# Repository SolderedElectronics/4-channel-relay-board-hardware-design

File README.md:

# 4-channel relay board  Hardware Design

## About the Product

|  |
| :----------------------------------------------------------: |
| [Buy 4-channel relay board ](https://www.solde.red/333022) |

Did you ever want to turn on and off a device that needs large current or voltage? Whether operating on DC or AC, a relay is what you need. A relay is actually an electronic switch that is activated by a signal we send from a Dasduino or Arduino. This module further simplifies the whole process because it contains everything you need for the relay to work, and you just have to connect it to the microcontroller and power supply. You don’t have to think about voltages and currents, insulation between high and low voltage or grounding, everything is already taken care of on the board. This product has 4 relays.

---

## Repository Contents

This repository contains all design files for 4-channel relay board , organized as follows:

- **`CAD` folder**: Contains KiCAD design files, including:
  - Schematics
  - PCB layout
  - Panel PCB layout
  - Source 3D files in Fusion360, if any
  - All files are sorted by version with a detailed change log.
- **`OUTPUTS` folder**: Includes all production-ready files, such as:
  - Bill of Materials (BOM) and interactive BOM (iBOM)
  - PDF versions of schematics
  - 3D `.step` file of the board
  - 3D-printable models
  - Gerber files for PCB manufacturing
  - Image of the pinout of the board
  - Product image
  - Compliance, legal and generic sales documents

Refer to the `Change Log` in the CAD folder for details about updates between versions.

---

## Learn More About the Product

Beyond the repository, explore the following resources:

### Soldered Verify

The **Soldered Verify** system ensures every board you purchase from Soldered is fully functional. It also provides access to exclusive test data for your product. To get started, find the unique Soldered Verify ID on your product's packaging and enter the ID on the [Soldered Verify page](https://soldered.com/verify/) to access test results and additional product details.

### Soldered Community

Soldered Community is your go-to place for technical support. Our engineers track and answer all questions posted there, and it’s a great space for the maker community. Get answers to your questions and solutions for your challenges at [Soldered Community](https://soldered.com/community).

### solde.red

solde.red is an ultimate URL shortener and information hub. Access it by typing solde.red/ followed by your product SKU, e.g., [solde.red/333000](https://solde.red/333000), to find getting-started guides, datasheets, open-source hardware and software files, certifications, images, pinouts, and more. Read more about the shortener [here](https://solde.red/info/).

---

## Contributing

Contributions are welcome! Here’s how you can get involved:

- Submit pull requests to enhance the design or fix issues.
- Report bugs or problems by opening an issue.

We encourage community collaboration to make this product even better.

---

## About Soldered

[Soldered for Makers](https://soldered.com) specializes in designing and manufacturing electronic products tailored for enthusiasts, ranging from hobbyists to professionals. Our portfolio includes electronic boards, sensors, and actuators that are widely utilized in fields such as microelectronics, mechatronics, robotics, programming, and IoT. Every product we offer is designed in-house and built upon open-source hardware and software platforms. Proudly certified and manufactured within the European Union, our catalog likely includes the product you need for your project.

We complement these products with comprehensive tutorials and manuals, product descriptions, schematics, programming codes, and project examples. Our round-the-clock [customer and technical support](https://soldered.com/community) is available for all our products, irrespective of the sales channel. Soldered’s success and services reflect our maker community’s unwavering [trust](https://www.trustpilot.com/review/soldered.com), for which we are deeply grateful. Join our community and create using Soldered products.

---

## License

All Soldered open-source hardware (OSH) is under The TAPR Open Hardware License. Read more in the LICENSE file located in this repository.

**Disclaimer:**

No warranty - all designs in this repository are distributed in the hope that they will be useful, but without any warranty. They are provided "AS IS", therefore without warranty of any kind, either expressed or implied. The entire quality and performance of what you do with the contents of this repository are your responsibility. In no event Soldered Electronics will be liable for your damages, or losses, including any general, special, incidental, or consequential damage arising out of the use or inability to use the contents of this repository. 

---

## Have fun!

Thank you for your support from your fellow makers at Soldered Electronics.

Happy Making!

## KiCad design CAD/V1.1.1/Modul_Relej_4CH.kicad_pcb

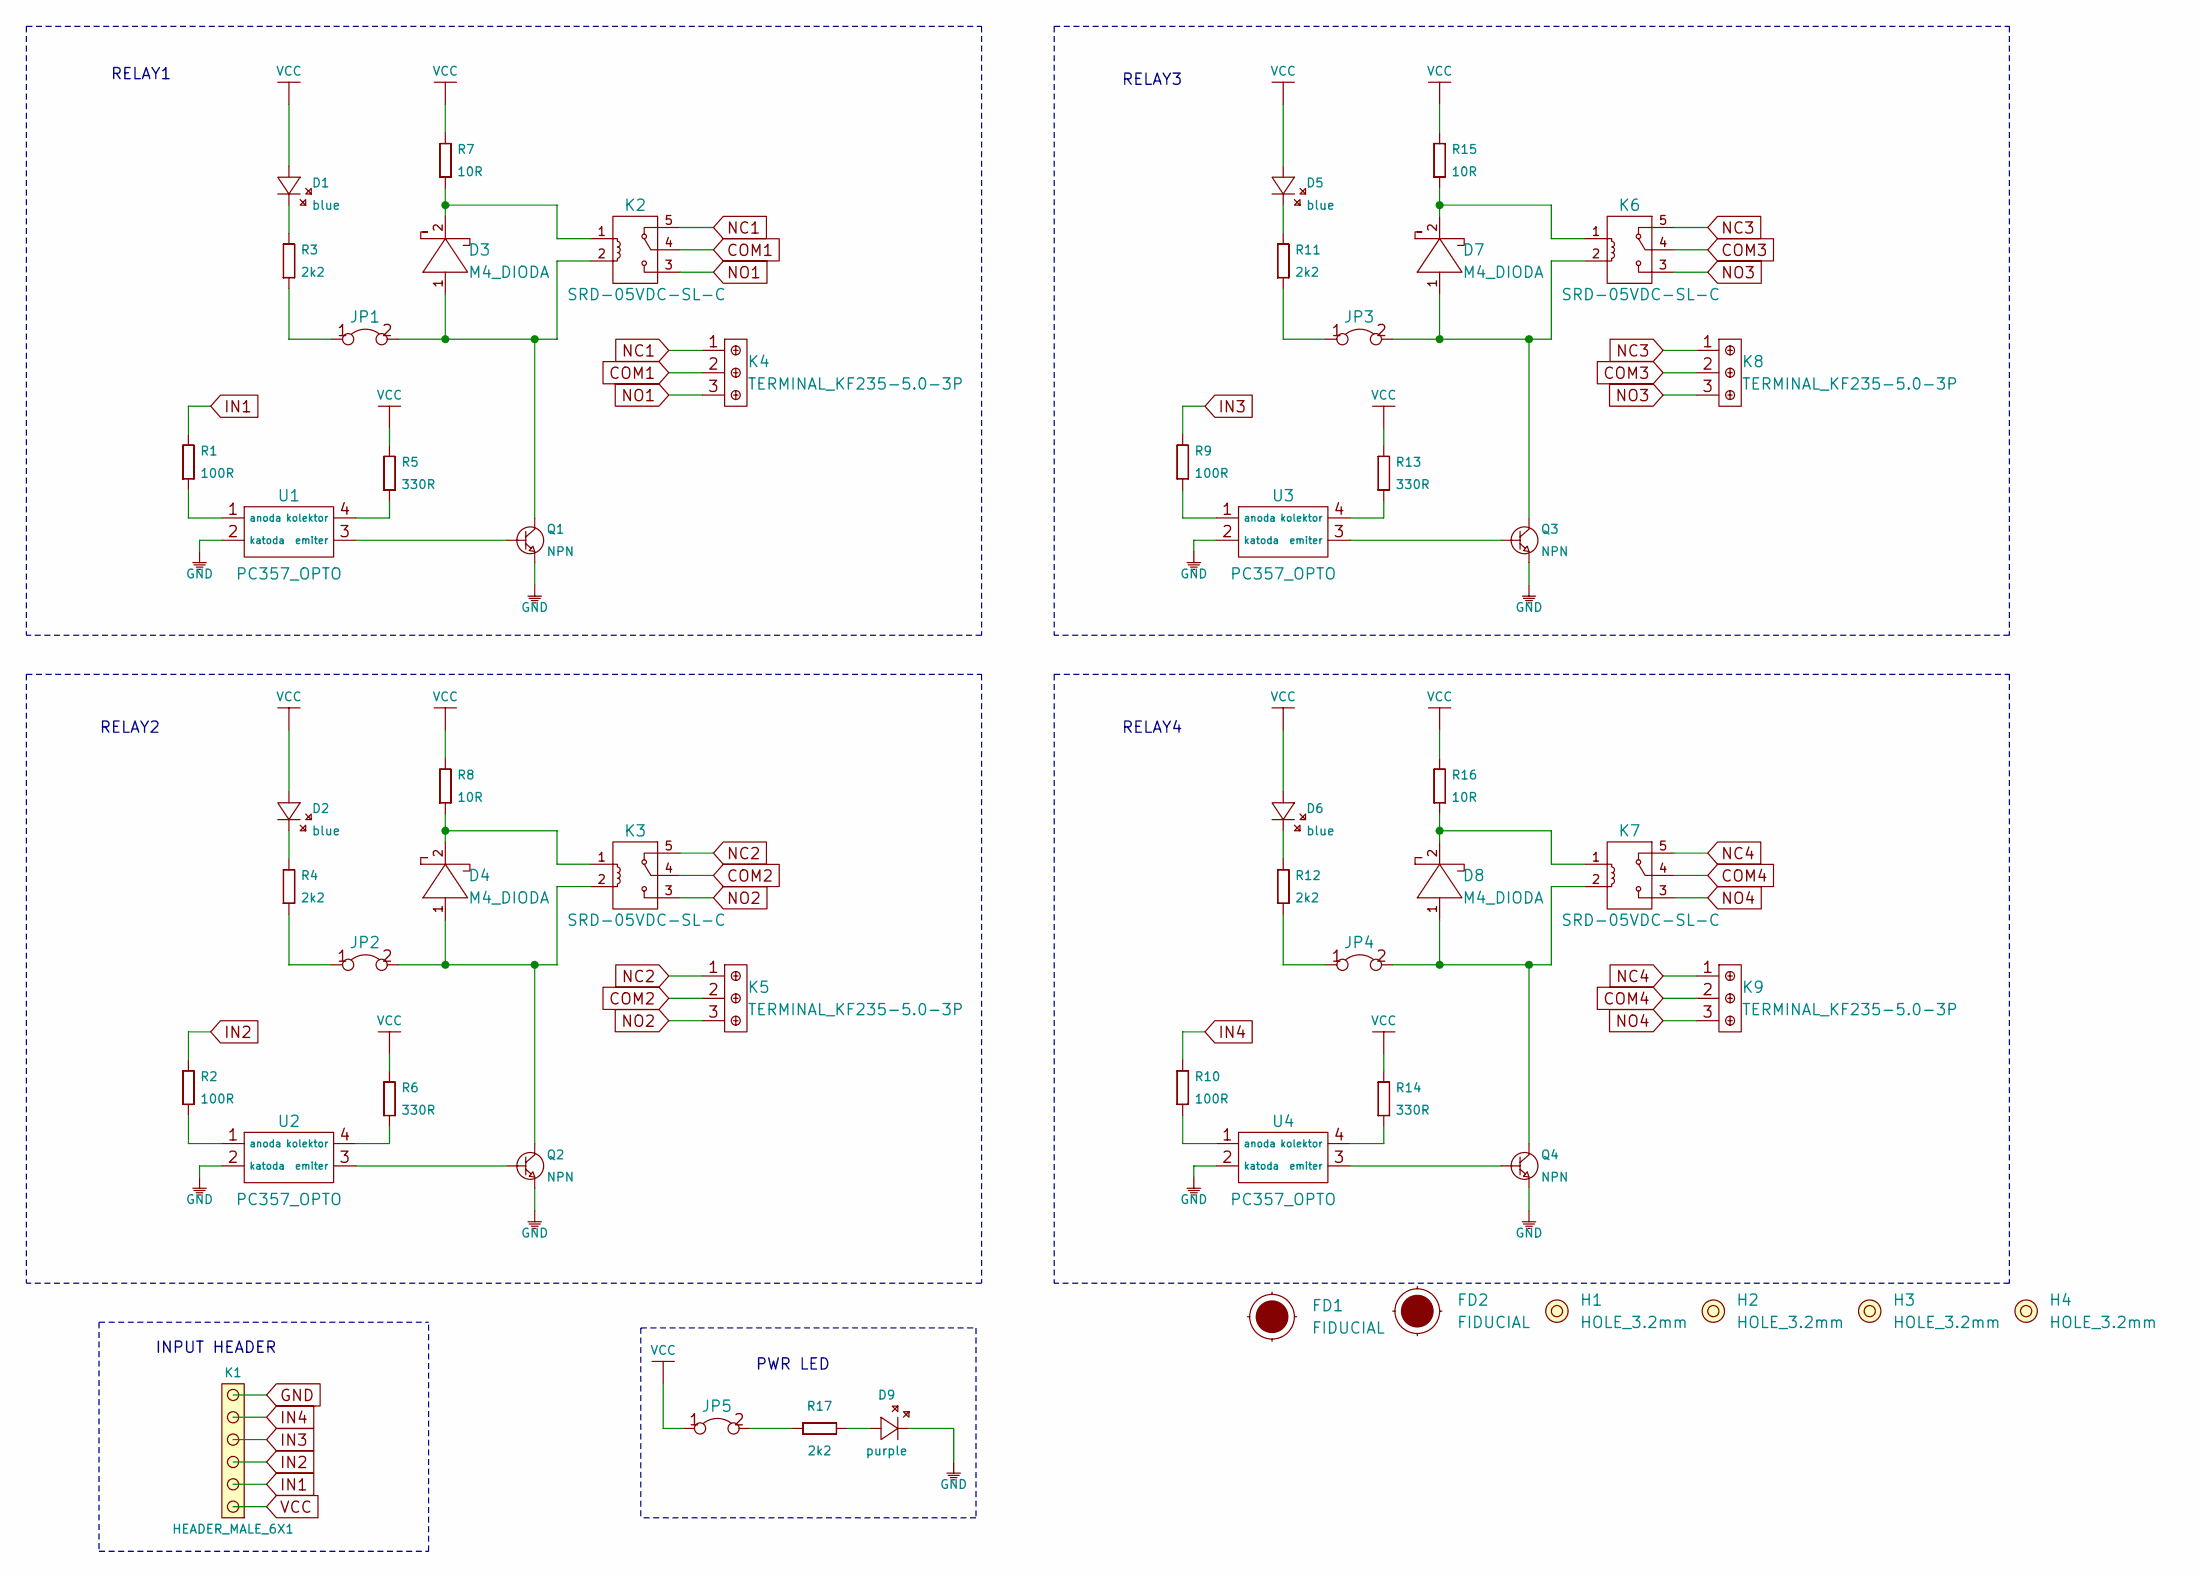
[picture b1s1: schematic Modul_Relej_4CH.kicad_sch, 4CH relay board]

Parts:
D1, D2, D5, D6: blue; 0402LED
D3, D4, D7, D8: M4_DIODA
D9: purple; 0402LED
FD1, FD2: FIDUCIAL; FIDUCIAL_23
H1, H2, H3, H4: HOLE_3.2mm
JP1, JP2, JP3, JP4, JP5: SMD-JUMPER-CONNECTED_TRACE_SLODERMASK
K1: HEADER_MALE_6X1
K2, K3, K6, K7: SRD-05VDC-SL-C; SRD_RELAY_5V
K4, K5, K8, K9: TERMINAL_KF235-5.0-3P
Q1, Q2, Q3, Q4: NPN; SOT-23-3
R1, R2, R9, R10: 100R; 0603R
R3, R4, R11, R12, R17: 2k2; 0402R
R5, R6, R13, R14: 330R; 0603R
R7, R8, R15, R16: 10R; 0603R
U1, U2, U3, U4: PC357_OPTO

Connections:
COM1: K2.4, K4.2
COM2: K3.4, K5.2
COM3: K6.4, K8.2
COM4: K7.4, K9.2
GND: D9.2 (K), K1.6, Q1.2 (E), Q2.2 (E), Q3.2 (E), Q4.2 (E), U1.2 (katoda), U2.2 (katoda), U3.2 (katoda), U4.2 (katoda)
IN1: K1.2, R1.2
IN2: K1.3, R2.2
IN3: K1.4, R9.2
IN4: K1.5, R10.2
NC1: K2.5, K4.1
NC2: K3.5, K5.1
NC3: K6.5, K8.1
NC4: K7.5, K9.1
NO1: K2.3, K4.3
NO2: K3.3, K5.3
NO3: K6.3, K8.3
NO4: K7.3, K9.3
unnamed: D1.2 (K), R3.2
unnamed: D2.2 (K), R4.2
unnamed: D3.1 (A), JP1.2, K2.2, Q1.3 (C)
unnamed: D3.2 (K), K2.1, R7.1
unnamed: D4.1 (A), JP2.2, K3.2, Q2.3 (C)
unnamed: D4.2 (K), K3.1, R8.1
unnamed: D5.2 (K), R11.2
unnamed: D6.2 (K), R12.2
unnamed: D7.1 (A), JP3.2, K6.2, Q3.3 (C)
unnamed: D7.2 (K), K6.1, R15.1
unnamed: D8.1 (A), JP4.2, K7.2, Q4.3 (C)
unnamed: D8.2 (K), K7.1, R16.1
unnamed: D9.1 (A), R17.2
unnamed: JP1.1, R3.1
unnamed: JP2.1, R4.1
unnamed: JP3.1, R11.1
unnamed: JP4.1, R12.1
unnamed: JP5.2, R17.1
unnamed: Q1.1 (B), U1.3 (emiter)
unnamed: Q2.1 (B), U2.3 (emiter)
unnamed: Q3.1 (B), U3.3 (emiter)
unnamed: Q4.1 (B), U4.3 (emiter)
unnamed: R1.1, U1.1 (anoda)
unnamed: R2.1, U2.1 (anoda)
unnamed: R5.1, U1.4 (kolektor)
unnamed: R6.1, U2.4 (kolektor)
unnamed: R9.1, U3.1 (anoda)
unnamed: R10.1, U4.1 (anoda)
unnamed: R13.1, U3.4 (kolektor)
unnamed: R14.1, U4.4 (kolektor)
VCC: D1.1 (A), D2.1 (A), D5.1 (A), D6.1 (A), JP5.1, K1.1, R5.2, R6.2, R7.2, R8.2, R13.2, R14.2, R15.2, R16.2

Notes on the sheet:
RELAY3
RELAY2
INPUT HEADER
PWR LED
RELAY1
RELAY4

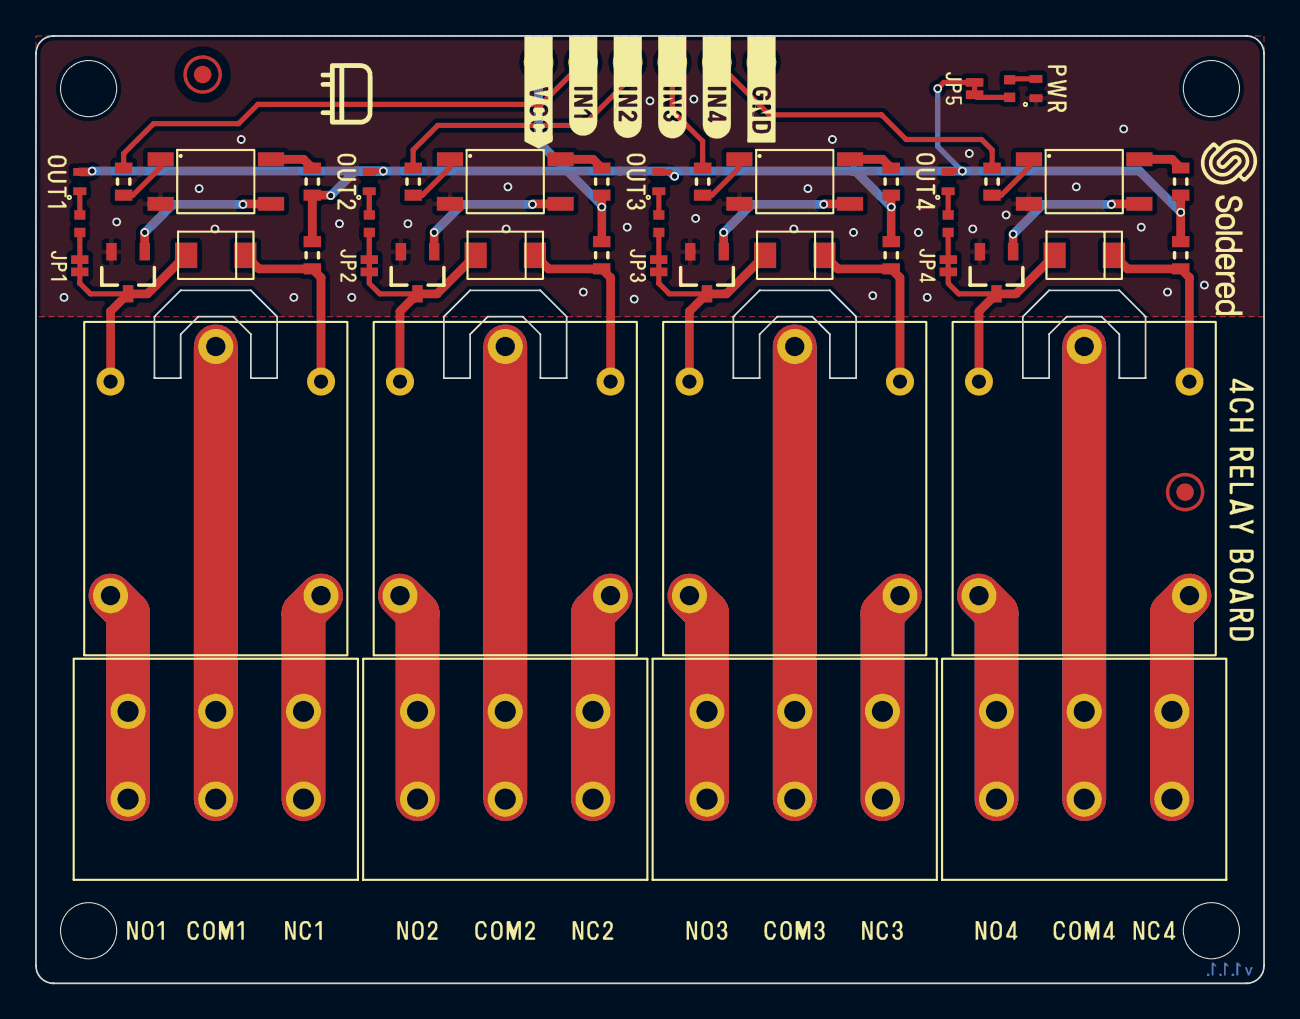
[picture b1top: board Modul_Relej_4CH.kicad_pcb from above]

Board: 2 copper layers, 70.0 x 54.0 mm, 54 parts (1 on the bottom side), 48 nets.

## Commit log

2022-08-06 Updating open source files.
